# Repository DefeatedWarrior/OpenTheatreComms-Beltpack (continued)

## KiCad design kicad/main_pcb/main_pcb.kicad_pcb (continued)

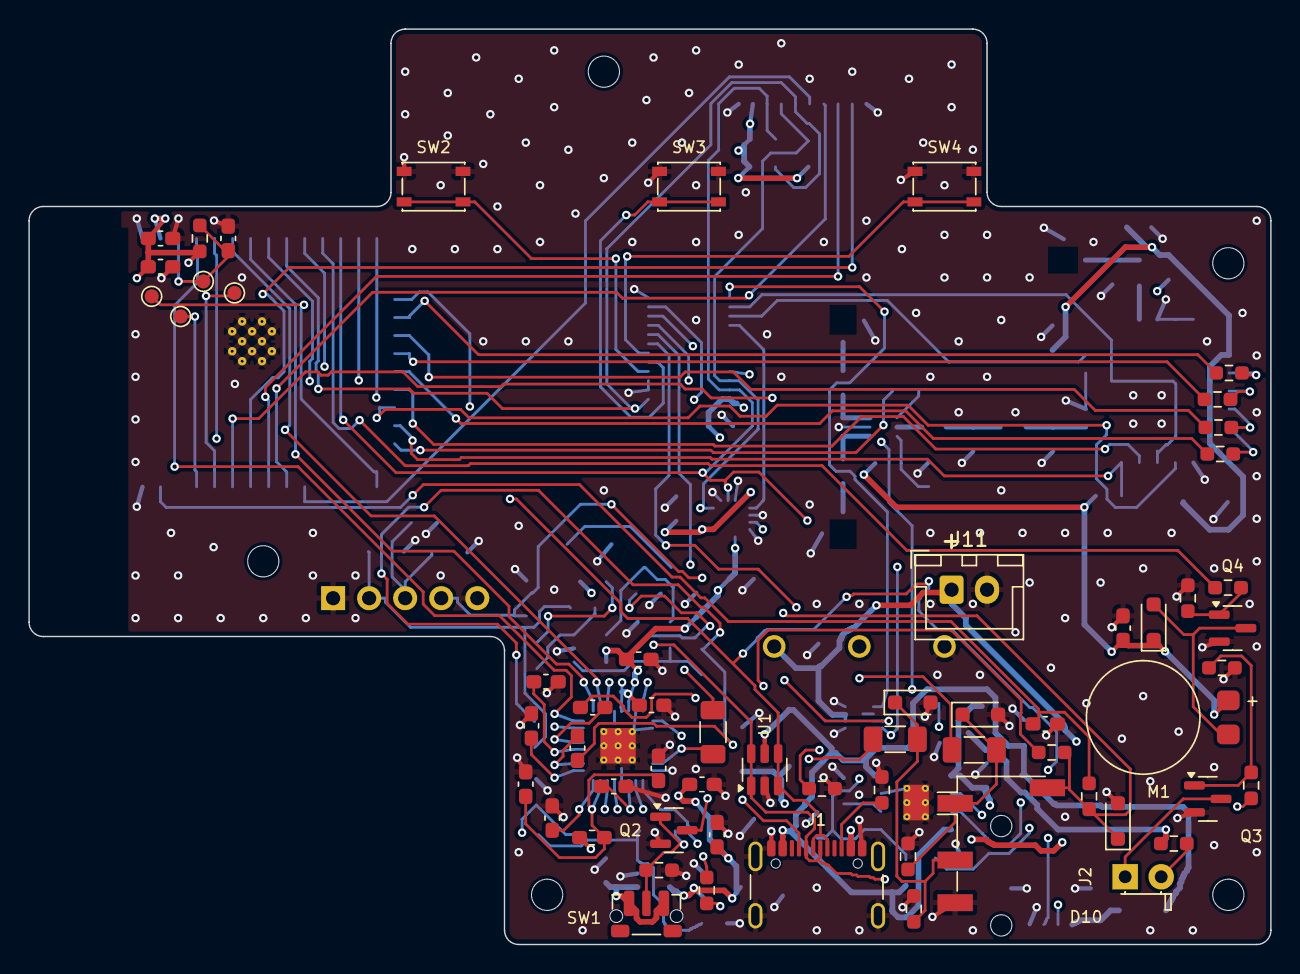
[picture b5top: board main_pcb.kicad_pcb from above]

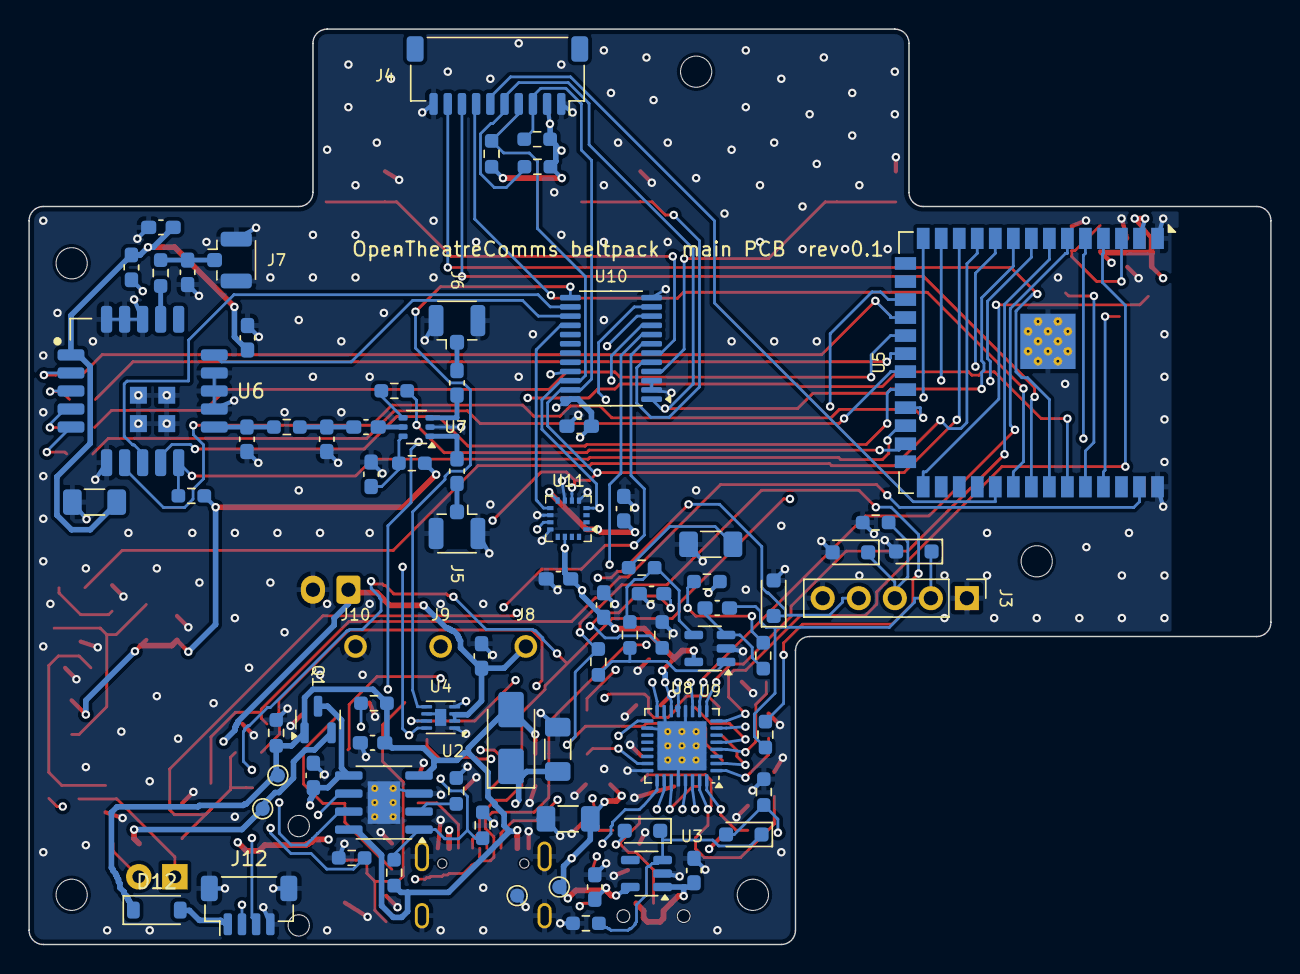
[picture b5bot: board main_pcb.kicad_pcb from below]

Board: 4 copper layers, 87.5 x 64.5 mm, 145 parts (80 on the bottom side), 98 nets.

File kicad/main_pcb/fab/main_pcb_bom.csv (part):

Qty,References,Value,Footprint,Part,Side,Notes
9,C1 C2 C5 C8 C12 C21 C25 C42 C43,10u,C_0603_1608Metric_Pad1.08x0.95mm_HandSolder,0603 X5R 10 V,bottom/top,
2,C3 C6,22u,C_1206_3216Metric_Pad1.33x1.80mm_HandSolder,1206 X5R 10 V,bottom,
6,C4 C10 C29 C30 C37 C38,1u,C_0603_1608Metric_Pad1.08x0.95mm_HandSolder,0603 X5R 10 V,bottom/top,
9,C7 C9 C13 C17 C22 C24 C26 C40 C41,100n,C_0603_1608Metric_Pad1.08x0.95mm_HandSolder,0603 X7R,bottom/top,
1,C11,47u,C_1206_3216Metric_Pad1.33x1.80mm_HandSolder,1206 X5R 6.3 V,bottom,Module bulk (guide: 47u + 10u + 100n)
0,C14 C15 C20,DNP DNP,C_0603_1608Metric_Pad1.08x0.95mm_HandSolder,"0603 C0G, tune",bottom,Not fitted. 
3,C16 C18 C19,100p,C_0603_1608Metric_Pad1.08x0.95mm_HandSolder,0603 C0G 50 V,bottom,
3,C23 C27 C28,4.7u,C_0603_1608Metric_Pad1.08x0.95mm_HandSolder,0603 X5R 10 V,top,
0,C31,DNP 1u,C_0603_1608Metric_Pad1.08x0.95mm_HandSolder,0603 X5R 10 V,bottom,Not fitted. 
0,C32,DNP 10u,C_0603_1608Metric_Pad1.08x0.95mm_HandSolder,0603 X5R 10 V,bottom,Not fitted. 
0,C33,DNP 22u,C_1206_3216Metric_Pad1.33x1.80mm_HandSolder,1206 X5R 6.3 V,bottom,Not fitted. 
0,C34,DNP 100n,C_0603_1608Metric_Pad1.08x0.95mm_HandSolder,0603 X7R,bottom,Not fitted. 
2,C35 C36,100u,C_1206_3216Metric_Pad1.33x1.80mm_HandSolder,1206 X5R 6.3 V,top,
1,C39,10n,C_0603_1608Metric_Pad1.08x0.95mm_HandSolder,0603 X7R,top,
1,D1,SS14,D_SMA,SS14 (SMA),bottom,Power path: USB feeds the system while the charger fills the cell
3,D2 D3 D11,BAT54WS,D_SOD-323_HandSoldering,Diodes BAT54WS,bottom/top,
6,D4 D5 D6 D7 D8 D9,PESD5V0S1BA,D_SOD-323_HandSoldering,Nexperia PESD5V0S1BA,bottom/top,
1,D10,White 3 mm,LED_D3.0mm_Horizontal_O1.27mm_Z2.0mm,"3 mm white LED, 20 mA",top,"Flashlight: legs bent 90 degrees, 2 mm above the board, through the bottom face"
1,D12,B5819W,D_SOD-123,B5819W (SOD-123),bottom,Dock power into VBUS; keeps USB-C's 5 V off the exposed dock contacts
1,FB1,600R,L_0603_1608Metric_Pad1.05x0.95mm_HandSolder,Murata BLM18PG601SN1D,top,
1,FB2,0R,L_0603_1608Metric_Pad1.05x0.95mm_HandSolder,0603 0R (or Murata BLM18PG121SN1D),bottom,Radio supply link: the module has its own ferrite; fit a 120R bead here only if 3V3 noise needs it
1,J1,USB-C,USB_C_Receptacle_GCT_USB4105-xx-A_16P_TopMnt_Horizontal,GCT USB4105-GF-A,top,"USB 2.0 Type-C receptacle: charging, firmware and USB serial"
1,J2,3.5 mm TRRS,Jack_3.5mm_PJ320D_Horizontal,PJ-320D,top,"3.5 mm headset jack, stereo out, electret mic in (CTIA)"
1,J3,XLR-4 wires,PinHeader_1x05_P2.54mm_Vertical,Neutrik NC4MD-L-1 (wired),bottom,"Wire pads for the panel XLR-4 male: 1 mic common, 2 mic +, 3 ear -, 4 ear +, 5 shell"
1,J4,Top PCB link,JST_SH_SM10B-SRSS-TB_1x10-1MP_P1.00mm_Horizontal,JST SM10B-SRSS-TB,bottom,"Side-entry JST SH 10, mouth up; same pinout as the top PCB's J1"
1,J5,Antenna A,U.FL_Hirose_U.FL-R-SMT-1_Vertical,Hirose U.FL-R-SMT-1(10),bottom,Antenna A (right-end flex antenna)
1,J6,Antenna B,U.FL_Hirose_U.FL-R-SMT-1_Vertical,Hirose U.FL-R-SMT-1(10),bottom,Antenna B (left-end flex antenna)
0,J7,DNP 2.4 GHz,U.FL_Hirose_U.FL-R-SMT-1_Vertical,Hirose U.FL-R-SMT-1(10),bottom,Not fitted. 2.4 GHz fallback antenna: footprint only in v1
1,J8,Battery +,MillMax_0906_SpringPin,Xinyangze YZ08415060P-02,bottom,"Spring pin onto the pack pad board (4.5 mm free, 4.0 working, 3.7 fully in; 0.8 mm tail): Battery +"
1,J9,Pack NTC,MillMax_0906_SpringPin,Xinyangze YZ08415060P-02,bottom,"Spring pin onto the pack pad board (4.5 mm free, 4.0 working, 3.7 fully in; 0.8 mm tail): Pack NTC"
1,J10,Battery -,MillMax_0906_SpringPin,Xinyangze YZ08415060P-02,bottom,"Spring pin onto the pack pad board (4.5 mm free, 4.0 working, 3.7 fully in; 0.8 mm tail): Battery -"
1,J11,Battery (JST XH),JST_XH_B2B-XH-A_1x02_P2.50mm_Vertical,JST B2B-XH-A(LF)(SN),top,Battery input in parallel with the spring pins (pin 1 +). A cell here has no NTC: fit R5 to turn the charger's temperature check off
1,J12,Dock,JST_SH_SM04B-SRSS-TB_1x04-1MP_P1.00mm_Horizontal,JST SM04B-SRSS-TB(LF)(SN),bottom,"Dock: cable to the contact board in the case bottom (1 VBUS, 2 D+, 3 D-, 4 GND)"
1,L1,0,R_0603_1608Metric_Pad0.98x0.95mm_HandSolder,0603 0R or RF inductor,bottom,Pi match series element: 0R until tuned
0,L2,DNP 0,R_0603_1608Metric_Pad0.98x0.95mm_HandSolder,0603 0R or RF inductor,bottom,Not fitted. 2.4 GHz match series element
1,M1,Vibration,Motor_Coin_8mm_LeadPads,"8 x 2.7 mm coin vibration motor, 3 V",top,Call alert
1,Q1,AO3401A,SOT-23,AOS AO3401A,bottom,Power path: battery to system when USB is absent (gate held at VBUS when present)
1,Q2,BSS138,SOT-23,onsemi BSS138,top,Reads the power button (low when pressed)
2,Q3 Q4,AO3400A,SOT-23,AOS AO3400A,top,
2,R1 R2,5.1k,R_0603_1608Metric_Pad0.98x0.95mm_HandSolder,0603 1%,top,
1,R3,1.5k,R_0603_1608Metric_Pad0.98x0.95mm_HandSolder,0603 1%,bottom,Charge current: about 1200/R3 A (1.5k = 800 mA; 2.4k = 500 mA)
1,R4,6.2k,R_0603_1608Metric_Pad0.98x0.95mm_HandSolder,0603 1%,bottom,NTC divider top: charging allowed from about 2 to 44 C with a 10k B3435 pack NTC
0,R5 R26 R29,DNP 0,R_0603_1608Metric_Pad0.98x0.95mm_HandSolder,0603 1%,bottom,Not fitted. 
8,R6 R7 R8 R11 R17 R33 R36 R38,100k,R_0603_1608Metric_Pad0.98x0.95mm_HandSolder,0603 1%,bottom/top,
4,R9 R12 R30 R31,10k,R_0603_1608Metric_Pad0.98x0.95mm_HandSolder,0603 1%,bottom/top,
1,R10,33k,R_0603_1608Metric_Pad0.98x0.95mm_HandSolder,0603 1%,bottom,
4,R13 R14 R15 R16,470,R_0603_1608Metric_Pad0.98x0.95mm_HandSolder,0603 1%,top,
2,R18 R19,1k,R_0603_1608Metric_Pad0.98x0.95mm_HandSolder,0603 1%,bottom,
2,R20 R28,0,R_0603_1608Metric_Pad0.98x0.95mm_HandSolder,0603 1%,bottom/top,
0,R21,DNP 100k,R_0603_1608Metric_Pad0.98x0.95mm_HandSolder,0603 1%,bottom,Not fitted. 
0,R22 R23 R41,DNP 10k,R_0603_1608Metric_Pad0.98x0.95mm_HandSolder,0603 1%,bottom,Not fitted. 
0,R24,DNP 47k,R_0603_1608Metric_Pad0.98x0.95mm_HandSolder,0603 1%,bottom,Not fitted. 
0,R25,DNP 2.2k,R_0603_1608Metric_Pad0.98x0.95mm_HandSolder,0603 1%,bottom,Not fitted. 
1,R27,0,R_1206_3216Metric_Pad1.30x1.75mm_HandSolder,1206 0R,top,BTL link (or a 100u 1206 cap for single-ended)
1,R32,2.2k,R_0603_1608Metric_Pad0.98x0.95mm_HandSolder,0603 1%,top,Electret bias
1,R34,56,R_0603_1608Metric_Pad0.98x0.95mm_HandSolder,0603 1%,top,About 20 mA at 4.2 V; dim with PWM
2,R35 R37,100,R_0603_1608Metric_Pad0.98x0.95mm_HandSolder,0603 1%,top,
0,R39 R40,DNP 4.7k,R_0603_1608Metric_Pad0.98x0.95mm_HandSolder,0603 1%,bottom,Not fitted. 
1,SW1,Power,SW_Push_1P1T-MP_NO_Horizontal_Alps_SKRTLAE010,Alps SKRTLAE010,top,"Side-push power button on the bottom edge: hold to switch on or off, tap for the flashlight"
1,SW2,Back,SW_SPST_PTS810,C&K PTS815 SJM 250 SMTR LFS,top,Front button: Back
1,SW3,Function,SW_SPST_PTS810,C&K PTS815 SJM 250 SMTR LFS,top,Front button: Function
1,SW4,Menu,SW_SPST_PTS810,C&K PTS815 SJM 250 SMTR LFS,top,Front button: Menu
1,U1,USBLC6-2SC6,SOT-23-6,ST USBLC6-2SC6,top,USB data and VBUS ESD
1,U2,TP4056,SOIC-8-1EP_3.9x4.9mm_P1.27mm_EP2.29x3mm_ThermalVias,TOPPOWER TP4056 (ESOP-8),bottom,"Li-ion charger, about 800 mA with R3 = 1.5k"
1,U3,TLV75733,SOT-23-5,TI TLV75733PDBVR,bottom,"3.3 V, 1 A LDO; EN is the soft power switch"
1,U4,MAX17048,TDFN-8-1EP_2x2mm_P0.5mm_EP0.8x1.2mm,Analog MAX17048G+T10,bottom,"Battery fuel gauge on the cell directly, I2C 0x36"
1,U5,ESP32-S3-WROOM-1-N8R8,ESP32-S3-WROOM-1,Espressif ESP32-S3-WROOM-1-N8R8,bottom,"MCU: Opus, radio timing, UI. Antenna end over the no-copper strip"
1,U6,LR2021,LR2021_Elecrow_10x10mm,Elecrow LR2021 module (LMM16121D),bottom,915-928 MHz FLRC radio; 2.4 GHz port for fallback
1,U7,PE4259,SOT-363_SC-70-6,pSemi PE4259-63,bottom,"Antenna diversity switch, RF1 = antenna A when CTRL is high"
1,U8,NAU88C22,QFN-32-1EP_5x5mm_P0.5mm_EP3.45x3.45mm_ThermalVias,Nuvoton NAU88C22YG,bottom,"Codec, I2C 0x1A, MODE low = 2-wire. Mics up to about 55 dB gain, BTL output for XLR earpieces"
0,U9,DNP OPA365,SOT-23-5,TI OPA365AIDBVR,bottom,"Not fitted. Optional dynamic-mic preamp (slot, unfitted)"
1,U10,TCA9555PWR,TSSOP-24_4.4x7.8mm_P0.65mm,TI TCA9555PWR,bottom,"IO expander at 0x21 (A0 high): buttons, charger, power button, sensors"
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
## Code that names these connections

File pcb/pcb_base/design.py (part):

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      "18": "GND", "19": "GND", "20": "GND"}
comp("U4", "OpenTheatreComms:LR2021_Module_Elecrow", "LR2021", "OpenTheatreComms:LR2021_Elecrow_10x10mm", lr, B, pcb=("F", 53.0, 19.0, 90),
     mpn="Elecrow LR2021 module (LMM16121D)", desc="915-928 MHz FLRC radio; 2.4 GHz port for fallback")
for ref, a, b_, pin in (("R4", "LR_NSS", "LR_NSS_M", "2"), ("R5", "LR_SCK", "LR_SCK_M", "3"), ("R6", "LR_MOSI", "LR_MOSI_M", "4"), ("R7", "LR_MISO", "LR_MISO_M", "5")):
    R(ref, "470", a, b_, B, near=("U4", pin, "F"), desc="SPI series resistor (module guide)")
R("R8", "100k", "+3V3", "LR_NRESET", B, near=("U4", "10", "F"))
comp("FB1", "Device:FerriteBead_Small", "0R", "Inductor_SMD:L_0603_1608Metric_Pad1.05x0.95mm_HandSolder", {"1": "+3V3", "2": "LR_VDD"}, B,
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Cap("C14", "100p", "RF_LF_M", "RF_SW_C", B, mpn="0603 C0G 50 V", desc="DC block (switch RFC)")
comp("U5", "OpenTheatreComms:PE4259", "PE4259", "Package_TO_SOT_SMD:SOT-363_SC-70-6",
     {"5": "RF_SW_C", "4": "RF_CTRL_S", "6": "RF_SW_VDD", "1": "RF_SW_1", "3": "RF_SW_2", "2": "GND"}, B,
     mpn="pSemi PE4259-63", desc="Antenna diversity switch, RF1 = antenna A when CTRL is high")
R("R9", "1k", "RF_CTRL", "RF_CTRL_S", B, near=("U5", "4", "F"))
R("R10", "1k", "+3V3", "RF_SW_VDD", B, near=("U5", "6", "F"))
Cap("C15", "100n", "RF_SW_VDD", "GND", B, near=("U5", "6", "F"))
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           "15": p_ + "TXRX_EN", "16": None, "17": None, "18": "GND", "19": "GND", "20": "GND"}
    comp(u, "OpenTheatreComms:LR2021_Module_Elecrow", "LR2021", "OpenTheatreComms:LR2021_Elecrow_10x10mm", lrk, B, pcb=("F", ux, 19.0, 90),
         mpn="Elecrow LR2021 module (LMM16121D)", desc=f"Radio {k}: footprint only in v1", dnp=True)
    for i, (a, b_, pin) in enumerate(((p_ + "NSS", p_ + "NSS_M", "2"), ("LR_SCK", p_ + "SCK_M", "3"), ("LR_MOSI", p_ + "MOSI_M", "4"), ("LR_MISO", p_ + "MISO_M", "5"))):
        R(f"R{rb + i}", "470", a, b_, B, near=(u, pin, "F"), desc=f"Radio {k} SPI series resistor", dnp=True)
    R(f"R{rb + 4}", "100k", "+3V3", p_ + "NRESET", B, near=(u, "10", "F"), desc=f"Radio {k} reset pull-up", dnp=True)
    comp(f"FB{k}", "Device:FerriteBead_Small", "0R", "Inductor_SMD:L_0603_1608Metric_Pad1.05x0.95mm_HandSolder", {"1": "+3V3", "2": p_ + "VDD"}, B,
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
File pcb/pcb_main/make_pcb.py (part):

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u7 = fps["U7"]; orient(u7, "B", 0, 0, lambda f: pad1(f, "5")[0] > pad1(f, "1")[0] + 1)
shift_pad(u7, "5", pad1(c16, "2")[0] - 1.75, Y); done("U7")
rf1, rf2 = pad1(u7, "1"), pad1(u7, "3")
for pin, cref, jref, net_sw, net_ant in (("1", "C18", "J5", "RF_SW_1", "RF_ANT_A"), ("3", "C19", "J6", "RF_SW_2", "RF_ANT_B")):
    p = pad1(u7, pin); s = 1 if p[1] > Y else -1
    cx, cy = p[0] - 1.9, p[1] + s * 1.6
    cap = place_rf(cref, vert_up if s < 0 else vert_dn, "1", cx, cy)           # pad 1 toward the switch row
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run_escapes([("U11", "10", 0.2, 0), ("U11", "11", 0.2, -1), ("U11", "9", 0.2, 1), ("U11", "6", 0.2, 0), ("U11", "4", 0.2, 0)])  # accelerometer (0.5 mm LGA; its middle GND pin first)

# codec support parts: each one next to the fan via of the codec pin it serves, front side first (the front is free over
# the codec), so VREF, MICBIAS, the analog supply and the mic coupling all stay within a couple of millimetres of their pins
for t_ in b.GetTracks():
    if t_.GetClass() == "PCB_VIA":
        g_ = Point(*Bf(t_.GetPosition())).buffer(0.5); side_obst["F"].append(g_); side_obst["B"].append(g_)
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
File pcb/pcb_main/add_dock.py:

"""Add the dock connection to the finished main board.

J12  JST SH 4-pin vertical (BM04B-SRSS-TB) on the back face at the bottom edge, below the battery pack (pack underside
     y -31), so its plug points backward into the 5 mm strip under the pack. A flat 4-wire cable runs back from it to the
     dock contact board lying in the case bottom, where the dock's spring pins land.
D12  B5819W Schottky, DOCK_VBUS (anode) -> VBUS (cathode). Dock power charges the pack like USB-C does. The diode stops
     USB-C's 5 V from reaching the exposed contacts when a cable is plugged in. D+/D- are shared with the USB-C (full
     speed, short stub); U1 (USBLC6) already protects them.

Places both parts in free space (J12 near the USB-C, D12 next to J12 pin 1), then maze.py routes DOCK_VBUS, VBUS,
USB_DP and USB_DN. J12's ground pin and mounting pads get vias into the ground pour.

  python3 add_dock.py board.kicad_pcb
"""
import os, sys, math
import pcbnew
HERE = os.path.dirname(os.path.abspath(__file__)); sys.path.insert(0, HERE)
from pcbgeom import P, Bf, mm, MM, Copper, polyset_to_shapely, LAYERS
from shapely.geometry import Point, LineString

path = sys.argv[1]
b = pcbnew.LoadBoard(path)
if any(f.GetReference() in ("J12", "D12") for f in b.GetFootprints()): sys.exit("dock parts already on the board")
FP = "/usr/share/kicad/footprints"
def load(lib, name, ref, val):
    f = pcbnew.FootprintLoad(f"{FP}/{lib}.pretty", name); f.SetReference(ref); f.SetValue(val)
    f.SetFPID(pcbnew.LIB_ID(lib, name)); b.Add(f); return f
dock = pcbnew.NETINFO_ITEM(b, "/DOCK_VBUS"); b.Add(dock)
N = lambda n: b.FindNet(n)
j = load("Connector_JST", "JST_SH_BM04B-SRSS-TB_1x04-1MP_P1.00mm_Vertical", "J12", "Dock")
d = load("Diode_SMD", "D_SOD-123", "D12", "B5819W")
jn = {"1": "/DOCK_VBUS", "2": "/USB_DP", "3": "/USB_DN", "4": "GND", "MP": "GND"}
for p in j.Pads(): p.SetNet(N(jn[p.GetNumber()]))
for p in d.Pads(): p.SetNet(N("/VBUS" if p.GetNumber() == "1" else "/DOCK_VBUS"))
for f in (j, d): f.SetPosition(P(500, 500))
b.Save(path); b = pcbnew.LoadBoard(path)
j = [f for f in b.GetFootprints() if f.GetReference() == "J12"][0]; d = [f for f in b.GetFootprints() if f.GetReference() == "D12"][0]

# lone ground stitching vias in the strip under the pack: make room (the pours stay connected through the rest)
tracked = set()
for t in b.GetTracks():
    if t.GetClass() == "PCB_TRACK": tracked |= {(t.GetStart().x, t.GetStart().y), (t.GetEnd().x, t.GetEnd().y)}
removed = 0
for t in list(b.GetTracks()):
    if t.GetClass() == "PCB_VIA" and t.GetNetname() == "GND" and (t.GetPosition().x, t.GetPosition().y) not in tracked:
        vx, vy = Bf(t.GetPosition())
        if 20.5 < vx < 30.0 and vy < -31.5: b.Delete(t); removed += 1
print("stitching vias removed from the strip:", removed)
cu = Copper(b)
crt_of = lambda f, s: polyset_to_shapely(f.GetCourtyard(pcbnew.B_CrtYd if s == "B" else pcbnew.F_CrtYd))
def others(s, skip):
    o = [crt_of(f, "B" if f.IsFlipped() else "F") for f in b.GetFootprints()
         if f.GetReference() not in skip and not f.GetReference().startswith("TP") and (f.IsFlipped() == (s == "B") or f.GetReference().startswith("H"))]
    return o + [Point(*Bf(f.GetPosition())).buffer(2.7) for f in b.GetFootprints() if f.GetReference().startswith("H")]
keep = [polyset_to_shapely(z.Outline()) for z in b.Zones() if z.GetIsRuleArea()]
j1 = [f for f in b.GetFootprints() if f.GetReference() == "J1"][0]
usb_pts = [Bf(p.GetPosition()) for p in j1.Pads() if p.GetNetname() in ("/USB_DP", "/USB_DN")]
ucx, ucy = sum(x for x, _ in usb_pts) / len(usb_pts), sum(y for _, y in usb_pts) / len(usb_pts)
ymin = cu.edge.bounds[1]

def put(f, x, y, rot, side):
    f.SetPosition(P(x, y)); f.SetOrientationDegrees(0)
    if f.IsFlipped() != (side == "B"): f.Flip(P(x, y), False)
    f.SetOrientationDegrees(rot)
def fab_box(f):
    xs, ys = [], []
    for g in f.GraphicalItems():
        if g.GetLayer() in (pcbnew.F_Fab, pcbnew.B_Fab):
            r = g.GetBoundingBox(); xs += [pcbnew.ToMM(r.GetX()) - 150, pcbnew.ToMM(r.GetRight()) - 150]; ys += [105 - pcbnew.ToMM(r.GetY()), 105 - pcbnew.ToMM(r.GetBottom())]
    return min(xs), min(ys), max(xs), max(ys)
PACK_UNDERSIDE = -31.0
holes = [(*Bf(p.GetPosition()), mm(p.GetDrillSize().x) / 2) for f in b.GetFootprints() for p in f.Pads()
         if p.HasHole() and f.GetReference() not in ("J12", "D12")]          # pegs and leads poke through: keep the body off them                                           # battery pack: x -13.5..39.5, y -31..15, behind the board
def fits(f, side, obs, extra=(), edge=0.8):
    crt = crt_of(f, side)
    if (edge >= 0 and not cu.edge.buffer(-edge).contains(crt)) or any(k.intersects(crt) for k in keep): return None
    for p in f.Pads():                                           # copper at least 0.4 mm from the board edge
        if not cu.edge.buffer(-0.4).contains(polyset_to_shapely(p.GetEffectivePolygon())): return None
    if any(o.intersects(crt) for o in list(obs) + list(extra)): return None
    L = pcbnew.B_Cu if side == "B" else pcbnew.F_Cu
    for p in f.Pads():
        if not p.IsOnLayer(L): continue
        if not cu.clear(polyset_to_shapely(p.GetEffectivePolygon()), p.GetNetname(), [L], 0.22, pads_any_net=False): return None
    return crt

best = None
for side in ("B",):                                              # back face: the plug points into the strip under the pack
    obs_j = others(side, ("J12", "D12"))
    for x in [k * 0.5 for k in range(-26, 81)]:                  # x -13..40, under the pack
        for y in [k * 0.25 for k in range(-144, -123)]:          # y -36..-31
            for rot in (0, 180):                                 # pin row along the edge
                put(j, x, y, rot, side)
                body = fab_box(j)                                    # the housing (and the plug above it) must clear the pack
                if body[3] > PACK_UNDERSIDE - 0.3 or body[1] < cu.edge.bounds[1] + 0.1: continue
                if any(bx0 - 0.4 < hx < bx1 + 0.4 and by0 - 0.4 < hy < by1 + 0.4 for hx, hy, r in holes for bx0, by0, bx1, by1 in [body]): continue
                cj = fits(j, side, obs_j, edge=-3.0)                 # courtyard may overhang the edge; pads are checked
                if cj is None: continue
                p1 = Bf([p for p in j.Pads() if p.GetNumber() == "1"][0].GetPosition())
                score = math.hypot(x - ucx, y - ucy)
                if best and score >= best[0]: continue
                dbest = None
                for dside in ("B", "F"):
                    obs_d = others(dside, ("J12", "D12"))
                    for dx in [k * 0.5 for k in range(-16, 17)]:
                        for dy in [k * 0.5 for k in range(-4, 17)]:
                            for drot in (0, 90, 180, 270):
                                put(d, p1[0] + dx, p1[1] + dy, drot, dside)
                                if fits(d, dside, obs_d, [cj] if dside == "B" else []) is None: continue
                                a = Bf([p for p in d.Pads() if p.GetNumber() == "2"][0].GetPosition())
                                dd = math.dist(a, p1) + (1.5 if dside != "B" else 0)
                                if dbest is None or dd < dbest[0]: dbest = (dd, p1[0] + dx, p1[1] + dy, drot, dside)
                if dbest is None: continue
                best = (score, x, y, rot, side, dbest)
if best is None: sys.exit("no spot for J12/D12")
score, x, y, rot, side, (dd, dx, dy, drot, dside) = best
put(j, x, y, rot, side); put(d, dx, dy, drot, dside)
# ground vias next to J12 pin 4 and the mounting pads
cu = Copper(b)
L = pcbnew.B_Cu if side == "B" else pcbnew.F_Cu
def gnd_via(pad):
    c = Bf(pad.GetPosition())
    for r in (0.9, 1.1, 1.3, 1.6, 2.0):
        for k in range(16):
            a = 2 * math.pi * k / 16; vx, vy = c[0] + r * math.cos(a), c[1] + r * math.sin(a)
            if not cu.via_ok(vx, vy, "GND"): continue
            t = LineString([c, (vx, vy)])
            if not cu.clear(t.buffer(0.15), "GND", [L], 0.2, pads_any_net=False): continue
            v = pcbnew.PCB_VIA(b); v.SetPosition(P(vx, vy)); v.SetDrill(MM(0.3)); v.SetWidth(MM(0.6)); v.SetNet(N("GND")); b.Add(v)
            tr = pcbnew.PCB_TRACK(b); tr.SetStart(P(*c)); tr.SetEnd(P(vx, vy)); tr.SetLayer(L); tr.SetWidth(MM(0.3)); tr.SetNet(N("GND")); b.Add(tr)
            cu.add_track(v); cu.add_track(tr); return True
    return False
gv = [gnd_via(p) for p in j.Pads() if p.GetNetname() == "GND"]
b.Save(path)
print(f"J12 at ({x:.2f}, {y:.2f}) rot {rot} on {side} (body y {fab_box(j)[1]:.2f}..{fab_box(j)[3]:.2f}); D12 at ({dx:.1f}, {dy:.1f}) rot {drot} on {dside}; ground vias {gv}")
